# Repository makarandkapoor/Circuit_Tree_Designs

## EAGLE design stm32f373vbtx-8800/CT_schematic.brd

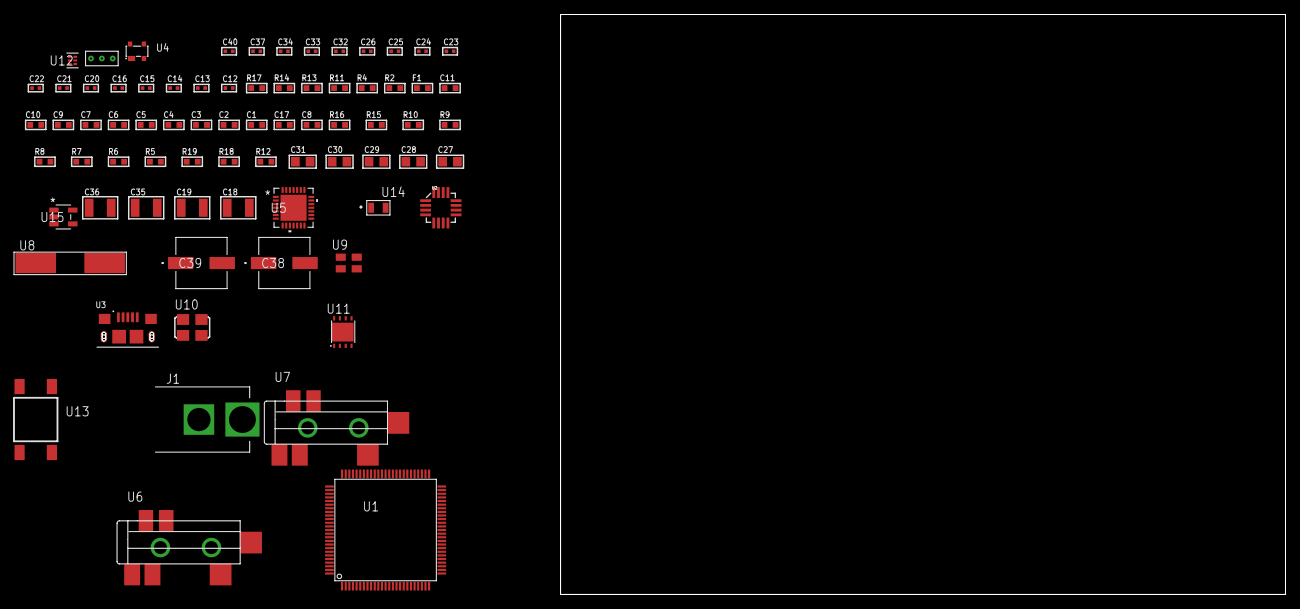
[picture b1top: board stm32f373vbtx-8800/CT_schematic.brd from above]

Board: 2 copper layers, 163.2 x 80.0 mm, 75 parts (0 on the bottom side), 36 nets, no tracks yet.

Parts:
C1, C11: 1e-06; C0603
C2, C3, C4, C5, C6, C7, C9: 1e-07; C0603
C8: 4.7e-06; C0603
C10: 1e-08; C0603
C12, C13: 1e-11; C0402
C14, C15, C16, C32, C33, C34, C40: 1e-08; C0402
C17: 4.7e-07; C0603
C18, C19: 2.2e-05; C1210
C20, C21: 1e-09; C0402
C22, C23, C24, C25, C26, C37: 1e-07; C0402
C27, C28, C29, C30, C31: 1e-05; C0805
C35, C36: 1e-05; C1210
C38, C39: 0.0001; EXV-9H
F1: 240.0; L0603
J1: PJ-037B; PJ-037B_PACKAGE
R2, R14: 1000.0; R0603
R4: 4700.0; R0603
R5, R6, R7, R15, R16: 10000.0; R0603
R8, R9, R10: 47000.0; R0603
R11: 680.0; R0603
R12: 100000.0; R0603
R13: 2231.0; R0603
R17: 9100.0; R0603
R18: 680000.0; R0603
R19: 120000.0; R0603
U1: STM32F373VBT7; LQFP100
U2: l3g4200d; LGA-16
U3: 10118193-0001LF; FCI_10118193-0001LF
U4: prtr5v0u2ax; SOT143B
U5: WM8731CLSEFL; QFN-28
U6, U7: SJ-43515TS-SMT-TR
U8: ABLS-25.000MHZ-B2F-T
U9: ASEK-32.768KHz-ECST; ASEK
U10: ASFL1-12.288MHZ-EC-T; ASFL1
U11: LP3878SDX-ADJ/NOPB; WSON-8
U12: TPS3895ADRYR; SON-6
U13: 4-1437565-2; SW_4-1437565-2
U14: Q65110A2395; LGM67K-G1J2-24-Z
U15: nc7sz125m5x; NC7SZ125M5X
U16: Dummy; DUMMY_PACKAGE_163

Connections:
CLK_CRYSTAL_U1_12: C12.1, U1.12, U8.1
CLK_CRYSTAL_U1_13: C13.1, U1.13, U8.2
CLK_U1_8: U1.8, U9.3
CLK_U5_1: U5.1, U10.3
GND: C1.2, C2.2, C3.2, C4.2, C5.2, C6.2, C7.2, C8.2, C9.2, C10.2, C11.2, C12.2, C13.2, C14.2, C15.2, C16.2, C21.2, C22.2, C23.2, C24.2, C25.2, C26.2, C27.2, C28.2, C29.2, C30.2, C31.2, C32.2, C33.2, C34.2, C35.2, C36.2, C37.2, C38.2, C39.2, C40.2, J1.2, R2.2, R5.2, R6.1, R6.2, R8.2, R9.2, R10.2, R14.2, R17.2, R19.2, U1.20, U1.74, U1.99, U2.8, U2.9, U2.10, U2.11, U2.12, U2.13, U3.5, U3.6, U3.7, U3.8, U3.9, U4.1, U5.4, U5.15, U5.19, U5.25, U5.26, U5.29, U6.1, U7.1, U9.2, U10.2, U11.3, U11.PAD, U12.2, U14.C, U15.1, U15.3, U16.1
NET_U1_14: R4.1, U1.14, U15.4
NET_U1_21: C10.1, C11.1, F1.1, U1.21, U1.22, U1.50, U1.51
NET_U1_49: C9.1, U1.48, U1.49
NET_U1_94: R5.1, U1.94
NET_U1_98: U13.3, U13.4
NET_U2_14: C16.1, C17.1, U2.14
NET_U4_4: U3.1, U4.4
NET_U5_20: C26.1, C31.1, U5.20
NET_U6_2: C19.1, R9.1, U6.2
NET_U6_5: C18.1, R8.1, U6.5
NET_U7_5: C20.1, C21.1, R10.1, R11.1, U7.5
NET_U11_1: C34.1, U11.1
NET_U11_6: R13.2, R14.1, U11.6
NET_U11_8: R12.1, U11.8
NET_U12_1: R16.1, R17.1, U12.1
NET_U12_3: R18.2, R19.1, U12.3
NET_U12_4: R15.1, U12.4, U15.2
NET_U13_1: R2.1, U13.1, U13.2
PROC_I2S1_CK: U1.64, U5.7
PROC_I2S1_SD: U1.35, U5.8
PROC_I2S1_WS: U1.63, U5.9, U5.11
PROC_PE2: U1.1, U16.2
PROC_PE3: U1.2, U16.3
PROC_SPI1_MISO: U1.31, U2.4
PROC_SPI1_MOSI: U1.32, U2.3
PROC_SPI1_NSS: R7.1, U1.29, U2.5
PROC_SPI1_SCK: U1.30, U2.2
PROC_USB_DM: U1.70, U3.2, U4.3
PROC_USB_DP: U1.71, U3.3, U4.2
VCC_S1_14V9: C35.1, C38.1, C39.1, J1.1, R12.2, U11.4
VCC_TIER1_3V3: C1.1, C2.1, C3.1, C4.1, C5.1, C6.1, C7.1, C8.1, C14.1, C15.1, C22.1, C23.1, C24.1, C25.1, C27.1, C28.1, C29.1, C30.1, C32.1, C33.1, C36.1, C37.1, C40.1, F1.2, R4.2, R7.2, R13.1, R15.2, R16.2, R18.1, U1.6, U1.28, U1.75, U1.100, U2.1, U2.15, U2.16, U5.3, U5.5, U5.12, U5.18, U9.4, U10.4, U11.5, U12.6, U15.5

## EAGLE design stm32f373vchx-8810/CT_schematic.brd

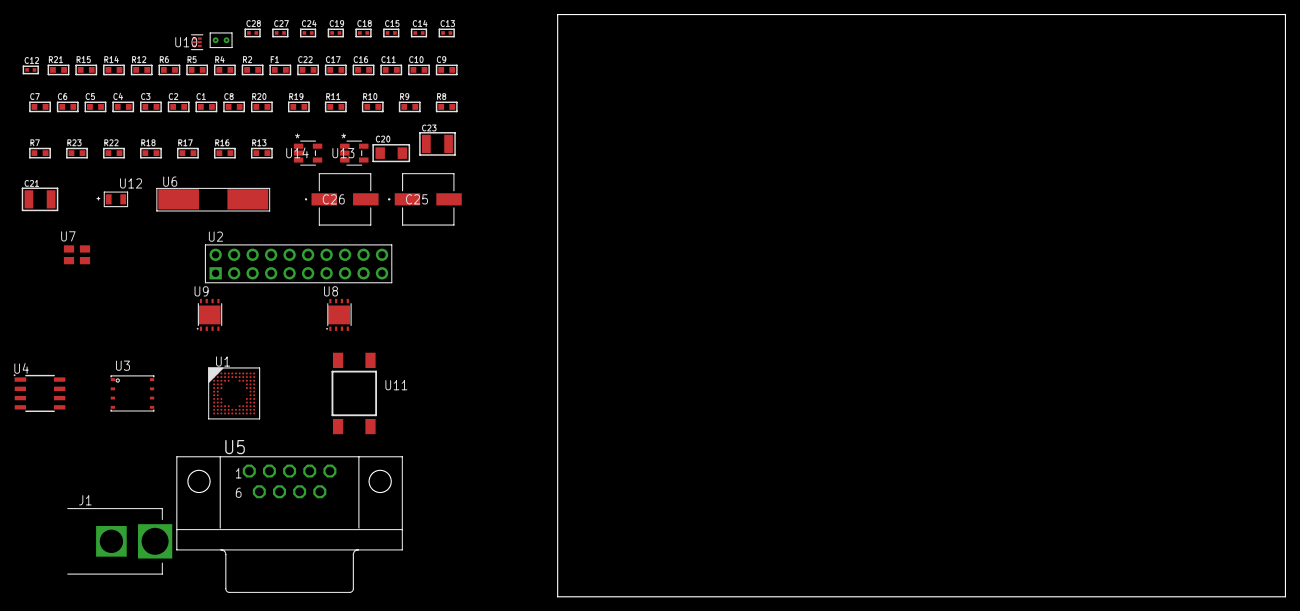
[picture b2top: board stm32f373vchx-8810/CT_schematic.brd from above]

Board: 2 copper layers, 100.0 x 80.0 mm, 66 parts (0 on the bottom side), 36 nets, no tracks yet.

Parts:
C1, C11, C16, C17, C22: 1e-06; C0603
C2, C3, C4, C5, C6, C7, C9: 1e-07; C0603
C8: 4.7e-06; C0603
C10: 1e-08; C0603
C12, C13: 1e-11; C0402
C14, C24: 1e-07; C0402
C15, C18, C19, C27, C28: 1e-08; C0402
C20: 1e-05; C1206
C21, C23: 1e-05; C1210
C25, C26: 0.0001; EXV-9H
F1: 240.0; L0603
J1: PJ-037B; PJ-037B_PACKAGE
R2, R15: 1000.0; R0603
R4: 4700.0; R0603
R5, R6: 2200.0; R0603
R7, R8, R9, R10, R11, R19, R20: 10000.0; R0603
R12: 120.0; R0603
R13, R16, R18: 100000.0; R0603
R14: 2231.0; R0603
R17: 300000.0; R0603
R21: 9100.0; R0603
R22: 680000.0; R0603
R23: 120000.0; R0603
U1: STM32F373VCH7; UFBGA100
U2: TST-110-05-T-D-RA
U3: 24AA512-I/MF; DFN8-S
U4: MCP2562-E/SN; SOIC-8
U5: 182-009-113R531; 182-009-MALE
U6: ABLS-25.000MHZ-B2F-T
U7: ASEK-32.768KHz-ECST; ASEK
U8: LP3878SDX-ADJ/NOPB; WSON-8
U9: LP2951ACSDX/NOPB; WSON-8
U10: TPS3895ADRYR; SON-6
U11: 4-1437565-2; SW_4-1437565-2
U12: Q65110A2395; LGM67K-G1J2-24-Z
U13, U14: nc7sz125m5x; NC7SZ125M5X
U15: Dummy; DUMMY_PACKAGE_149

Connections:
CLK_CRYSTAL_U1_F1: C12.1, U1.F1, U6.1
CLK_CRYSTAL_U1_G1: C13.1, U1.G1, U6.2
CLK_U1_D1: U1.D1, U7.3
GND: C1.2, C2.2, C3.2, C4.2, C5.2, C6.2, C7.2, C8.2, C9.2, C10.2, C11.2, C12.2, C13.2, C14.2, C15.2, C16.2, C17.2, C18.2, C19.2, C20.2, C21.2, C22.2, C23.2, C24.2, C25.2, C26.2, C27.2, C28.2, J1.2, R2.2, R7.2, R9.2, R10.2, R15.2, R18.2, R21.2, R23.2, U1.D3, U1.F11, U1.K1, U2.4, U2.6, U2.8, U2.10, U2.12, U2.14, U2.16, U2.18, U2.20, U3.4, U3.7, U4.2, U4.8, U5.5, U7.2, U8.3, U8.PAD, U9.3, U9.4, U9.PAD, U10.2, U12.C, U13.2, U13.3, U14.1, U14.3, U15.1
NET_U1_A3: R5.1, U1.A3, U3.6
NET_U1_A4: R7.1, U1.A4
NET_U1_B3: R6.1, U1.B3, U3.5
NET_U1_F12: C9.1, U1.F12, U1.L11
NET_U1_H2: R4.1, U1.H2, U14.4
NET_U1_M1: C10.1, C11.1, F1.1, U1.G12, U1.L1, U1.L12, U1.M1
NET_U1_M12: U11.3, U11.4
NET_U3_1: R9.1, U3.1
NET_U3_2: R10.1, U3.2
NET_U3_3: R11.1, U3.3
NET_U4_6: R12.2, U4.6
NET_U5_2: R12.2, U4.6, U5.2
NET_U5_3: R12.1, U4.7, U5.3
NET_U8_1: C19.1, U8.1
NET_U8_6: R14.2, R15.1, U8.6
NET_U8_8: R13.1, U8.8
NET_U9_5: R16.1, U9.5
NET_U9_7: R17.2, R18.1, U9.7
NET_U10_1: R20.1, R21.1, U10.1
NET_U10_3: R22.2, R23.1, U10.3
NET_U10_4: R19.1, U10.4, U13.4, U14.2
NET_U11_1: R2.1, U11.1, U11.2
PROC_CAN_RX: U1.B12, U4.4
PROC_CAN_TX: U1.A12, U4.1
PROC_DAC1_OUT2: U1.K4, U15.2
PROC_SYS_JTCK_SWCLK: U1.A10, U2.9
PROC_SYS_JTDO_TRACESWO: U1.A8, U2.13
PROC_SYS_JTMS_SWDIO: U1.A11, U2.7
RST_OUT_U2_SRESET_B: R8.1, U2.15, U13.1
VCC_S1_10V6: C20.1, C22.1, C25.1, C26.1, J1.1, R13.2, U8.4, U9.8
VCC_TIER1_3V3: C1.1, C2.1, C3.1, C4.1, C5.1, C6.1, C7.1, C8.1, C14.1, C15.1, C17.1, C18.1, C21.1, C24.1, C27.1, C28.1, F1.2, R4.2, R5.2, R6.2, R8.2, R11.2, R14.1, R19.2, R20.2, R22.1, U1.C4, U1.E2, U1.G11, U1.H3, U2.1, U3.8, U4.5, U7.4, U8.5, U10.6, U13.5, U14.5
VCC_TIER1_5V0: C16.1, C23.1, R16.2, R17.1, U4.3, U9.1

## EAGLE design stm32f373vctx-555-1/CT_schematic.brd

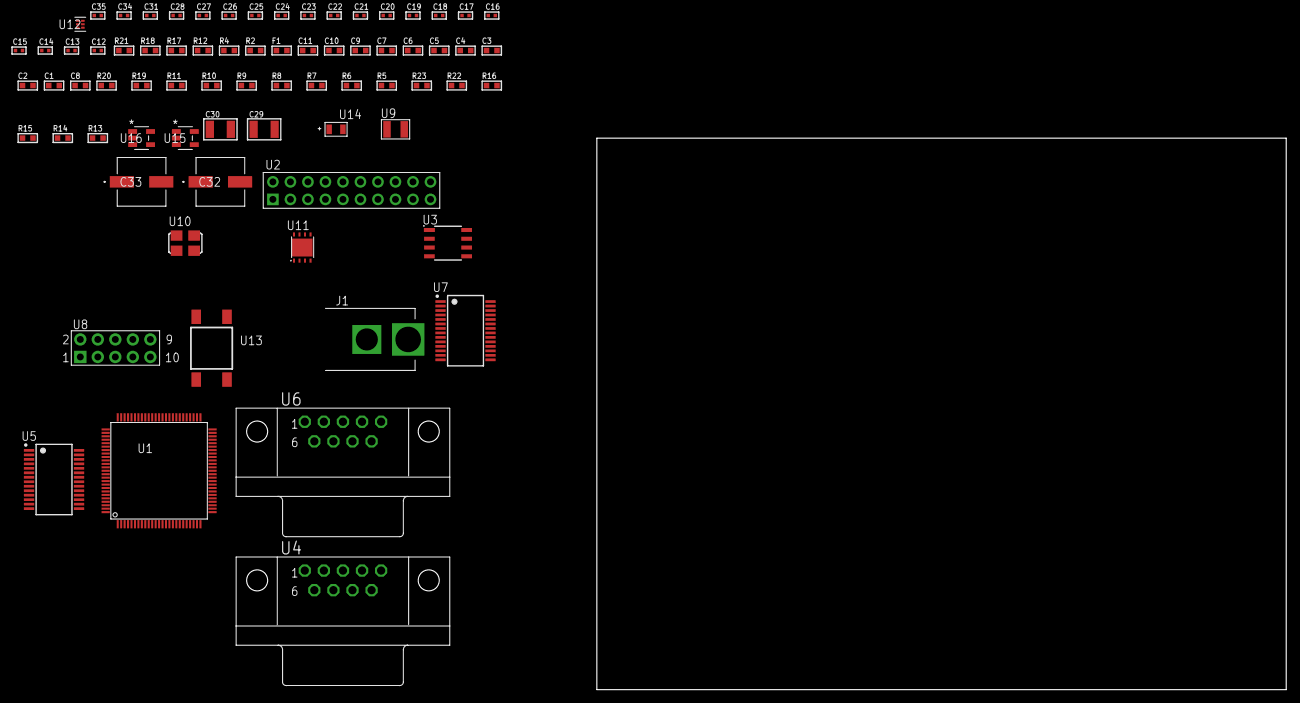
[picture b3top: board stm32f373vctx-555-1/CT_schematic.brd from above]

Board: 2 copper layers, 100.0 x 80.0 mm, 74 parts (0 on the bottom side), 61 nets, no tracks yet.

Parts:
C1, C11: 1e-06; C0603
C2, C3, C4, C5, C6, C7, C9: 1e-07; C0603
C8: 4.7e-06; C0603
C10: 1e-08; C0603
C12, C13: 1e-11; C0402
C14, C15, C16, C17, C18, C19, C20, C21, C22, C23, C24, C25, C26, C31: 1e-07; C0402
C27, C28, C34, C35: 1e-08; C0402
C29, C30: 1e-05; C1210
C32, C33: 0.0001; EXV-9H
F1: 240.0; L0603
J1: PJ-037B; PJ-037B_PACKAGE
R2, R18: 1000.0; R0603
R4: 4700.0; R0603
R5, R6, R7, R8, R9, R10, R11, R19, R20: 10000.0; R0603
R12: 120.0; R0603
R13: 470000.0; R0603
R14, R15, R16: 100000.0; R0603
R17: 2231.0; R0603
R21: 9100.0; R0603
R22: 680000.0; R0603
R23: 120000.0; R0603
U1: STM32F373VCT6; LQFP100
U2: TST-110-05-T-D-RA
U3: SN65HVD230D; SOIC-8
U4, U6: 182-009-113R531; 182-009-MALE
U5, U7: ST3241EBPR; SSOP-28
U8: HTSS-105-01-G-D
U9: ABS07-32.768KHZ-7-T
U10: ASFL1-25MHZ-NCS; ASFL1
U11: LP3878SDX-ADJ/NOPB; WSON-8
U12: TPS3895ADRYR; SON-6
U13: 4-1437565-2; SW_4-1437565-2
U14: Q65110A2395; LGM67K-G1J2-24-Z
U15, U16: nc7sz125m5x; NC7SZ125M5X

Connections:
CLK_CRYSTAL_U1_8: C12.1, U1.8, U9.1
CLK_CRYSTAL_U1_9: C13.1, U1.9, U9.2
CLK_U1_12: U1.12, U10.3
GND: C1.2, C2.2, C3.2, C4.2, C5.2, C6.2, C7.2, C8.2, C9.2, C10.2, C11.2, C12.2, C13.2, C14.2, C15.2, C16.2, C17.2, C20.2, C21.2, C22.2, C25.2, C26.2, C27.2, C28.2, C29.2, C30.2, C31.2, C32.2, C33.2, C34.2, C35.2, J1.2, R2.2, R5.2, R11.2, R13.2, R18.2, R21.2, R23.2, U1.20, U1.74, U1.99, U2.4, U2.6, U2.8, U2.10, U2.12, U2.14, U2.16, U2.18, U2.20, U3.2, U4.5, U5.23, U5.25, U6.5, U7.23, U7.25, U8.9, U10.2, U11.3, U11.PAD, U12.2, U14.C, U15.2, U15.3, U16.1, U16.3
NET_U1_14: R4.1, U1.14, U16.4
NET_U1_21: C10.1, C11.1, F1.1, U1.21, U1.22, U1.50, U1.51
NET_U1_49: C9.1, U1.48, U1.49
NET_U1_94: R5.1, U1.94
NET_U1_98: U13.3, U13.4
NET_U2_19: R11.1, U2.19
NET_U3_6: R12.2, U3.6
NET_U3_8: R13.1, U3.8
NET_U4_2: R12.2, U3.6, U4.2
NET_U4_3: R12.1, U3.7, U4.3
NET_U5_1: C19.1, U5.1
NET_U5_2: C19.2, U5.2
NET_U5_3: C21.1, U5.3
NET_U5_22: R14.1, U5.22
NET_U5_24: C18.2, U5.24
NET_U5_27: C20.1, U5.27
NET_U5_28: C18.1, U5.28
NET_U6_2: U5.4, U6.2
NET_U6_3: U5.9, U6.3
NET_U6_7: U5.5, U6.7
NET_U6_8: U5.10, U6.8
NET_U7_1: C24.1, U7.1
NET_U7_2: C24.2, U7.2
NET_U7_3: C26.1, U7.3
NET_U7_22: R15.1, U7.22
NET_U7_24: C23.2, U7.24
NET_U7_27: C25.1, U7.27
NET_U7_28: C23.1, U7.28
NET_U8_3: U7.4, U8.3
NET_U8_4: U7.5, U8.4
NET_U8_5: U7.9, U8.5
NET_U8_6: U7.10, U8.6
NET_U11_1: C28.1, U11.1
NET_U11_6: R17.2, R18.1, U11.6
NET_U11_8: R16.1, U11.8
NET_U12_1: R20.1, R21.1, U12.1
NET_U12_3: R22.2, R23.1, U12.3
NET_U12_4: R19.1, U12.4, U15.4, U16.2
NET_U13_1: R2.1, U13.1, U13.2
PROC_CAN_RX: U1.81, U3.4
PROC_CAN_TX: U1.82, U3.1
PROC_SYS_JTCK_SWCLK: R9.1, U1.76, U2.9
PROC_SYS_JTDI: R7.1, U1.77, U2.5
PROC_SYS_JTDO_TRACESWO: U1.89, U2.13
PROC_SYS_JTMS_SWDIO: R8.1, U1.72, U2.7
PROC_SYS_NJTRST: R6.1, U1.90, U2.3
PROC_USART1_CTS: U1.70, U5.13
PROC_USART1_RTS: U1.71, U5.18
PROC_USART1_RX: U1.34, U5.19
PROC_USART1_TX: U1.33, U5.14
PROC_USART2_CTS: U1.23, U7.13
PROC_USART2_RTS: U1.24, U7.18
PROC_USART2_RX: U1.26, U7.19
PROC_USART2_TX: U1.25, U7.14
RST_OUT_U2_SRESET_B: R10.1, U2.15, U15.1
VCC_S1_14V5: C29.1, C32.1, C33.1, J1.1, R16.2, U11.4
VCC_TIER1_3V3: C1.1, C2.1, C3.1, C4.1, C5.1, C6.1, C7.1, C8.1, C14.1, C15.1, C16.1, C17.1, C22.1, C27.1, C30.1, C31.1, C34.1, C35.1, F1.2, R4.2, R6.2, R7.2, R8.2, R9.2, R10.2, R14.2, R15.2, R17.1, R19.2, R20.2, R22.1, U1.6, U1.28, U1.75, U1.100, U2.1, U2.2, U3.3, U5.26, U7.26, U10.4, U11.5, U12.6, U15.5, U16.5

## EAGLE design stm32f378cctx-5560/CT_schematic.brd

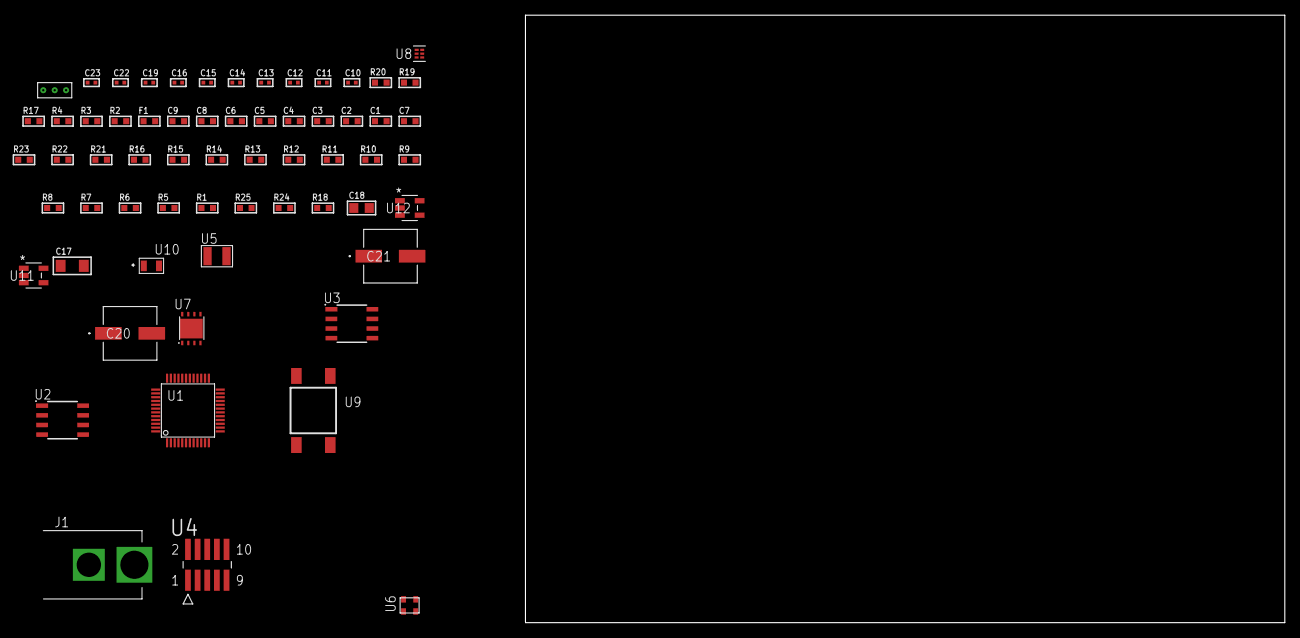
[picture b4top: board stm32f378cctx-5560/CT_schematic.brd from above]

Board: 2 copper layers, 100.0 x 80.0 mm, 63 parts (0 on the bottom side), 39 nets, no tracks yet.

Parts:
C1, C9: 1e-06; C0603
C2, C3, C4, C5, C6: 1e-07; C0603
C7: 4.7e-06; C0603
C8: 1e-08; C0603
C10, C11: 1e-11; C0402
C12, C13, C15, C16, C22, C23: 1e-08; C0402
C14, C19: 1e-07; C0402
C17: 1e-05; C1206
C18: 1e-05; C0805
C20, C21: 0.0001; EXV-9H
F1: 240.0; L0603
J1: PJ-037B; PJ-037B_PACKAGE
R1, R5, R6, R7, R8, R9, R10, R11, R12, R13, R14, R15, R16, R21, R22: 10000.0; R0603
R2, R20: 1000.0; R0603
R3: 910.0; R0603
R4: 4700.0; R0603
R17: 5.0; R0603
R18: 100000.0; R0603
R19: 806.0; R0603
R23: 82000.0; R0603
R24: 300000.0; R0603
R25: 120000.0; R0603
U1: STM32F378CCT6; LQFP48
U2: AT25160B-SSHL-T; SOIC-8
U3: AT25512N-SH-T; SOIC-8
U4: FTSH-105-01-L-DV-K; SAMTEC_FTSH-105-01-L-DV-K
U5: ABS07-32.768KHZ-7-T
U6: ASDMB-25.000MHZ-EC-T; ASDMB-XX.XXXXMHZ-XX-XX-XXX
U7: LP3878SDX-ADJ/NOPB; WSON-8
U8: TPS3895ADRYR; SON-6
U9: 4-1437565-2; SW_4-1437565-2
U10: Q65110A2395; LGM67K-G1J2-24-Z
U11, U12: nc7sz125m5x; NC7SZ125M5X
U13: Dummy; DUMMY_PACKAGE_132

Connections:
CLK_CRYSTAL_U1_3: C10.1, U1.3, U5.1
CLK_CRYSTAL_U1_4: C11.1, U1.4, U5.2
CLK_U1_5: U1.5, U6.3
GND: C1.2, C2.2, C3.2, C4.2, C5.2, C6.2, C7.2, C8.2, C9.2, C10.2, C11.2, C12.2, C13.2, C14.2, C15.2, C16.2, C17.2, C18.2, C19.2, C20.2, C21.2, C22.2, C23.2, J1.2, R2.2, R5.2, R6.2, R16.2, R17.2, R20.2, R23.2, R25.2, U1.8, U1.23, U1.47, U2.4, U3.4, U4.3, U4.5, U6.2, U7.3, U7.PAD, U8.2, U10.C, U11.2, U11.3, U12.1, U12.3, U13.1
NET_U1_7: R4.1, U1.7, U12.4
NET_U1_9: C8.1, C9.1, F1.1, U1.9, U1.24
NET_U1_20: R6.1, U1.20
NET_U1_44: R5.1, U1.44
NET_U1_45: R3.1, U1.45, U10.A
NET_U1_46: R1.1, U1.46, U9.3, U9.4
NET_U2_3: R7.1, U2.3
NET_U2_7: R9.1, U2.7
NET_U3_3: R10.1, U3.3
NET_U3_7: R12.1, U3.7
NET_U4_9: R17.1, U4.9
NET_U7_1: C16.1, U7.1
NET_U7_6: R19.2, R20.1, U7.6
NET_U7_8: R18.1, U7.8
NET_U8_1: R22.1, R23.1, U8.1
NET_U8_3: R24.2, R25.1, U8.3
NET_U8_4: R21.1, U8.4, U11.4, U12.2
NET_U9_1: R2.1, U9.1, U9.2
PROC_ADC1_IN1: U1.11, U13.3
PROC_ADC1_IN2: U1.12, U13.2
PROC_SPI1_MISO: U1.16, U3.2
PROC_SPI1_MOSI: U1.18, U3.5
PROC_SPI1_NSS: R11.1, U1.14, U3.1
PROC_SPI1_SCK: U1.15, U3.6
PROC_SPI2_MISO: U1.26, U2.2
PROC_SPI2_MOSI: U1.27, U2.5
PROC_SPI2_NSS: R8.1, U1.32, U2.1
PROC_SPI2_SCK: U1.28, U2.6
PROC_SYS_JTCK_SWCLK: R16.1, U1.37, U4.4
PROC_SYS_JTDI: R14.1, U1.38, U4.8
PROC_SYS_JTDO_TRACESWO: U1.39, U4.6
PROC_SYS_JTMS_SWDIO: R15.1, U1.34, U4.2
RST_OUT_U4_JTAG_RST_B: R13.1, U4.10, U11.1
VCC_S1_9V8: C17.1, C20.1, C21.1, J1.1, R18.2, U7.4
VCC_TIER1_1V8: C1.1, C2.1, C3.1, C4.1, C5.1, C6.1, C7.1, C12.1, C13.1, C14.1, C15.1, C18.1, C19.1, C22.1, C23.1, F1.2, R1.2, R3.2, R4.2, R7.2, R8.2, R9.2, R10.2, R11.2, R12.2, R13.2, R14.2, R15.2, R19.1, R21.2, R22.2, R24.1, U1.1, U1.17, U1.48, U2.8, U3.8, U4.1, U6.4, U7.5, U8.6, U11.5, U12.5

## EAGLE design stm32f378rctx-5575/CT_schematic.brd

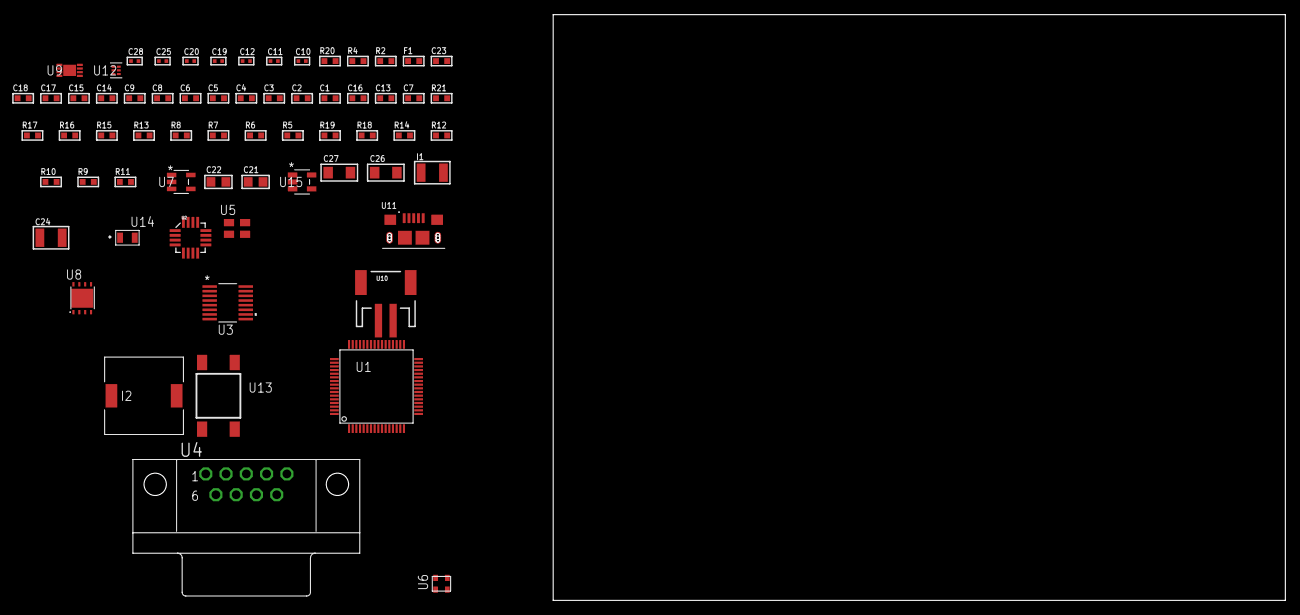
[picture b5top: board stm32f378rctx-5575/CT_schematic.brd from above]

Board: 2 copper layers, 122.6 x 80.0 mm, 65 parts (0 on the bottom side), 41 nets, no tracks yet.

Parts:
C1, C9, C14, C15, C17, C18, C23: 1e-06; C0603
C2, C3, C4, C5, C6: 1e-07; C0603
C7: 4.7e-06; C0603
C8: 1e-08; C0603
C10, C11, C12, C19, C20, C28: 1e-08; C0402
C13: 4.7e-07; C0603
C16: 2.2e-07; C0603
C21, C22: 1e-05; C0805
C24: 1e-05; C1210
C25: 1e-07; C0402
C26, C27: 1e-05; C1206
F1: 240.0; L0603
I1: 1e-05; L1210
I2: 5.2e-06; DR1040
R2: 1000.0; R0603
R4: 4700.0; R0603
R5, R6, R7, R8, R15, R16, R21: 10000.0; R0603
R9, R12, R14: 100000.0; R0603
R10: 490000.0; R0603
R11: 1000000.0; R0603
R13: 91000.0; R0603
R17: 82000.0; R0603
R18: 300000.0; R0603
R19: 120000.0; R0603
R20: 2000.0; R0603
U1: STM32F378RCT6; LQFP64
U2: l3g4200d; LGA-16
U3: LTC2804CGN-1#PBF; SSOP-16
U4: 182-009-113R531; 182-009-MALE
U5: ASEK-2-32.768KHz-ECST; ASEK
U6: ASDMB-25.000MHZ-EC-T; ASDMB-XX.XXXXMHZ-XX-XX-XXX
U7: ltc3406es5; TSOT-23-5
U8: LP2951ACSDX/NOPB; WSON-8
U9: MCP73831T-2ACI/MC; DFN8_2X3MC
U10: S2B-PH-SM4-TB(LF)(SN); JST-2-SMD
U11: 10118193-0001LF; FCI_10118193-0001LF
U12: TPS3895ADRYR; SON-6
U13: 4-1437565-2; SW_4-1437565-2
U14: Q65110A2395; LGM67K-G1J2-24-Z
U15: nc7sz125m5x; NC7SZ125M5X

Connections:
CLK_U1_3: U1.3, U5.3
CLK_U1_5: U1.5, U6.3
GND: C1.2, C2.2, C3.2, C4.2, C5.2, C6.2, C7.2, C8.2, C9.2, C10.2, C11.2, C12.2, C14.2, C15.2, C17.2, C18.2, C19.2, C20.2, C21.2, C22.1, C22.2, C23.2, C24.2, C25.2, C26.2, C27.2, C28.2, R2.2, R5.2, R6.2, R7.1, R7.2, R10.2, R14.2, R17.2, R19.2, R20.2, U1.12, U1.31, U1.63, U2.8, U2.9, U2.10, U2.11, U2.12, U2.13, U3.8, U4.5, U5.2, U6.2, U7.2, U8.3, U8.4, U8.PAD, U9.6, U9.9, U10.2, U11.5, U11.6, U11.7, U11.8, U11.9, U12.2, U14.C, U15.1, U15.3
INPUT_USBPOWER_5V: C26.1, R21.2, U9.1, U9.2, U11.1
NET_U1_7: R4.1, U1.7, U15.4
NET_U1_13: C8.1, C9.1, F1.1, U1.13, U1.17, U1.32
NET_U1_28: R6.1, U1.28
NET_U1_60: R5.1, U1.60
NET_U1_62: U13.3, U13.4
NET_U2_14: C12.1, C13.1, U2.14
NET_U3_6: C14.1, U3.6
NET_U3_7: C16.1, I1.2, U3.7
NET_U3_9: C15.1, U3.9
NET_U3_10: C16.2, U3.10
NET_U3_11: R9.1, U3.11
NET_U4_2: U3.1, U4.2
NET_U4_3: U3.3, U4.3
NET_U4_7: U3.2, U4.7
NET_U4_8: U3.4, U4.8
NET_U7_3: I2.1, U7.3
NET_U7_5: R10.1, R11.1, U7.5
NET_U7_ATNET_3: I2.2, R11.2
NET_U8_5: R12.1, U8.5
NET_U8_7: R13.2, R14.1, U8.7
NET_U9_5: R21.1, U9.5
NET_U9_8: R20.1, U9.8
NET_U12_1: R16.1, R17.1, U12.1
NET_U12_3: R18.2, R19.1, U12.3
NET_U12_4: R15.1, U12.4, U15.2
NET_U13_1: R2.1, U13.1, U13.2
PROC_SPI1_MISO: U1.22, U2.4
PROC_SPI1_MOSI: U1.23, U2.3
PROC_SPI1_NSS: R8.1, U1.20, U2.5
PROC_SPI1_SCK: U1.21, U2.2
PROC_USART1_CTS: U1.44, U3.13
PROC_USART1_RTS: U1.45, U3.15
PROC_USART1_RX: U1.25, U3.16
PROC_USART1_TX: U1.24, U3.14
VCC_S1_3V7: C21.1, C23.1, C27.1, U7.4, U8.8, U9.3, U9.4, U10.1
VCC_TIER1_1V8: C1.1, C2.1, C3.1, C4.1, C5.1, C6.1, C7.1, C11.1, C17.1, C18.1, C19.1, C20.1, C22.2, C25.1, C28.1, F1.2, I1.1, I2.2, R4.2, R8.2, R9.2, R11.2, R15.2, R16.2, R18.1, U1.1, U1.19, U1.64, U2.1, U3.5, U3.12, U5.4, U6.4, U12.6, U15.5
VCC_TIER1_2V5: C10.1, C24.1, R12.2, R13.1, U2.15, U2.16, U8.1

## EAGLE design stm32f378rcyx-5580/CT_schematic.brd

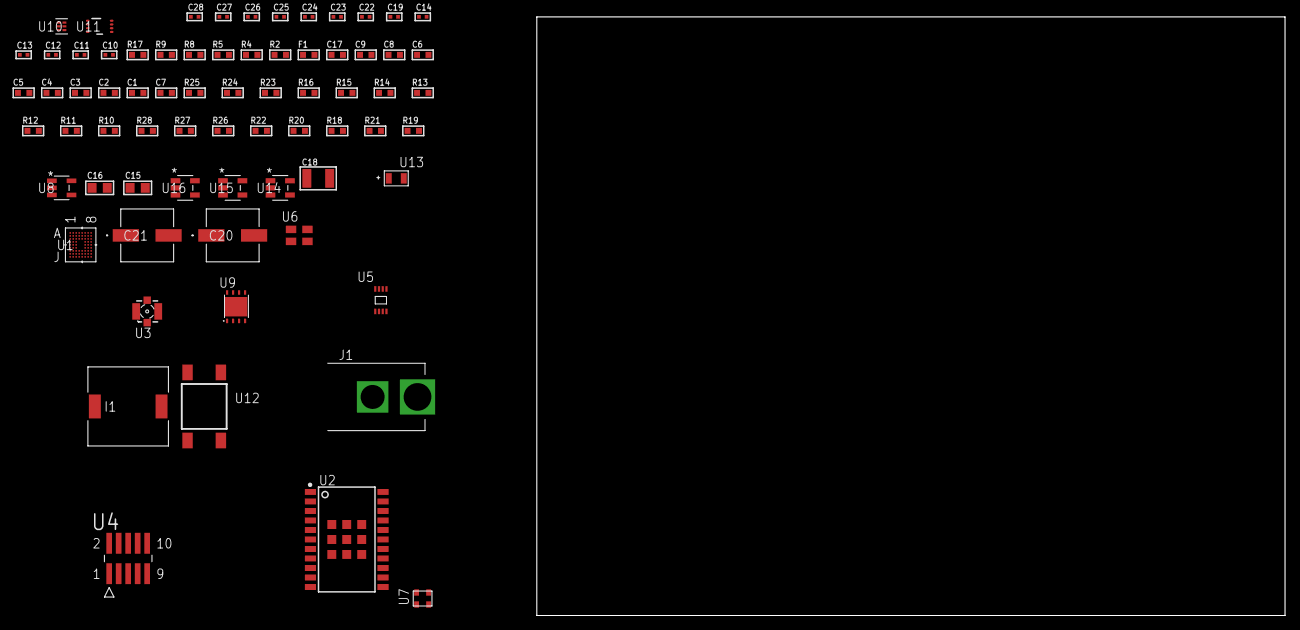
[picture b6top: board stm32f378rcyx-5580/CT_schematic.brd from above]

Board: 2 copper layers, 100.0 x 80.0 mm, 71 parts (0 on the bottom side), 36 nets, no tracks yet.

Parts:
C1, C9, C17: 1e-06; C0603
C2, C3, C4, C5, C6: 1e-07; C0603
C7: 4.7e-06; C0603
C8: 1e-08; C0603
C10, C11, C19, C23, C25: 1e-07; C0402
C12, C13, C14, C22, C24, C26, C27, C28: 1e-08; C0402
C15, C16: 1e-05; C0805
C18: 1e-05; C1210
C20, C21: 0.0001; EXV-9H
F1: 240.0; L0603
I1: 7e-06; DR1040
J1: PJ-037B; PJ-037B_PACKAGE
R2: 1000.0; R0603
R4, R5: 4700.0; R0603
R8, R9: 2200.0; R0603
R10, R11, R12, R13, R14, R15, R16, R23, R24: 10000.0; R0603
R17: 5.0; R0603
R18: 490000.0; R0603
R19: 1000000.0; R0603
R20, R22: 100000.0; R0603
R21: 153694.38; R0603
R25: 82000.0; R0603
R26: 300000.0; R0603
R27: 120000.0; R0603
R28: 200000.0; R0603
U1: STM32F378RCY6; WLCSP66_8X8
U2: A2200-A
U3: 73412-0114; COAXIAL_C
U4: FTSH-105-01-L-DV-K; SAMTEC_FTSH-105-01-L-DV-K
U5: 24AA04-I/MC; TDFN-8/6MM
U6: ASEK-2-32.768KHz-ECST; ASEK
U7: ASDMB-25.000MHZ-EC-T; ASDMB-XX.XXXXMHZ-XX-XX-XXX
U8: ltc3406es5; TSOT-23-5
U9: LP2951ACSDX/NOPB; WSON-8
U10: TPS3895ADRYR; SON-6
U11: LSF0102DCTR; DCU0008A_N
U12: 4-1437565-2; SW_4-1437565-2
U13: Q65110A2395; LGM67K-G1J2-24-Z
U14, U15, U16: nc7sz125m5x; NC7SZ125M5X

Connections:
CLK_U1_C8: U1.C8, U6.3
CLK_U1_D7: U1.D7, U7.3
GND: C1.2, C2.2, C3.2, C4.2, C5.2, C6.2, C7.2, C8.2, C9.2, C10.2, C11.2, C12.2, C13.2, C14.2, C15.2, C16.1, C16.2, C17.2, C18.2, C19.2, C20.2, C21.2, C22.2, C23.2, C24.2, C25.2, C26.2, C27.2, C28.2, J1.2, R2.2, R10.2, R11.2, R16.2, R17.2, R18.2, R22.2, R25.2, R27.2, U1.C6, U1.G4, U1.G5, U1.G8, U1.J1, U2.7, U2.8, U2.23, U2.24, U2.25, U2.26, U2.27, U2.28, U2.29, U2.30, U2.31, U4.3, U4.5, U5.4, U6.2, U7.2, U8.2, U9.3, U9.4, U9.PAD, U10.2, U11.1, U13.C, U14.2, U14.3, U15.1, U15.3, U16.1, U16.3
NET_U1_B1: R9.1, U1.B1, U5.5
NET_U1_B2: R8.1, U1.B2, U5.6
NET_U1_C7: R10.1, U1.C7
NET_U1_E7: R5.1, U1.E7, U16.4
NET_U1_G2: R11.1, U1.G2
NET_U1_G7: C8.1, C9.1, F1.1, U1.G6, U1.G7, U1.H1
NET_U1_J8: U12.3, U12.4
NET_U2_2: R12.2, U2.2
NET_U2_17: R12.1, U2.17
NET_U2_22: R4.1, U2.22, U15.4
NET_U3_1: U2.11, U3.1
NET_U3_2: U2.10, U3.2, U3.3, U3.4
NET_U4_9: R17.1, U4.9
NET_U8_3: I1.1, U8.3
NET_U8_5: R18.1, R19.1, U8.5
NET_U8_ATNET_3: I1.2, R19.2
NET_U9_5: R20.1, U9.5
NET_U9_7: R21.2, R22.1, U9.7
NET_U10_1: R24.1, R25.1, U10.1
NET_U10_3: R26.2, R27.1, U10.3
NET_U10_4: R23.1, U10.4, U14.4, U15.2, U16.2
NET_U11_8: R28.1, U11.8
NET_U12_1: R2.1, U12.1, U12.2
PROC_I2C1_SCL_TOXCVR: U2.15, U11.5
PROC_I2C1_SDA_TOXCVR: U2.16, U11.6
PROC_SYS_JTCK_SWCLK: R16.1, U1.A1, U4.4
PROC_SYS_JTDI: R14.1, U1.A2, U4.8
PROC_SYS_JTDO_TRACESWO: U1.C5, U4.6
PROC_SYS_JTMS_SWDIO: R15.1, U1.C4, U4.2
RST_OUT_U4_JTAG_RST_B: R13.1, U4.10, U14.1
VCC_S1_4V8: C15.1, C17.1, C20.1, C21.1, J1.1, U8.4, U9.8
VCC_TIER1_1V8: C1.1, C2.1, C3.1, C4.1, C5.1, C6.1, C7.1, C11.1, C12.1, C13.1, C14.1, C16.2, C19.1, C24.1, C25.1, C26.1, C27.1, C28.1, F1.2, I1.2, R5.2, R8.2, R9.2, R13.2, R14.2, R15.2, R19.2, R23.2, R24.2, R26.1, U1.A8, U1.D6, U1.J7, U4.1, U5.7, U5.8, U6.4, U7.4, U10.6, U11.2, U14.5, U15.5, U16.5
VCC_TIER1_3V3: C10.1, C18.1, C22.1, C23.1, R4.2, R20.2, R21.1, R28.2, U2.20, U9.1, U11.7

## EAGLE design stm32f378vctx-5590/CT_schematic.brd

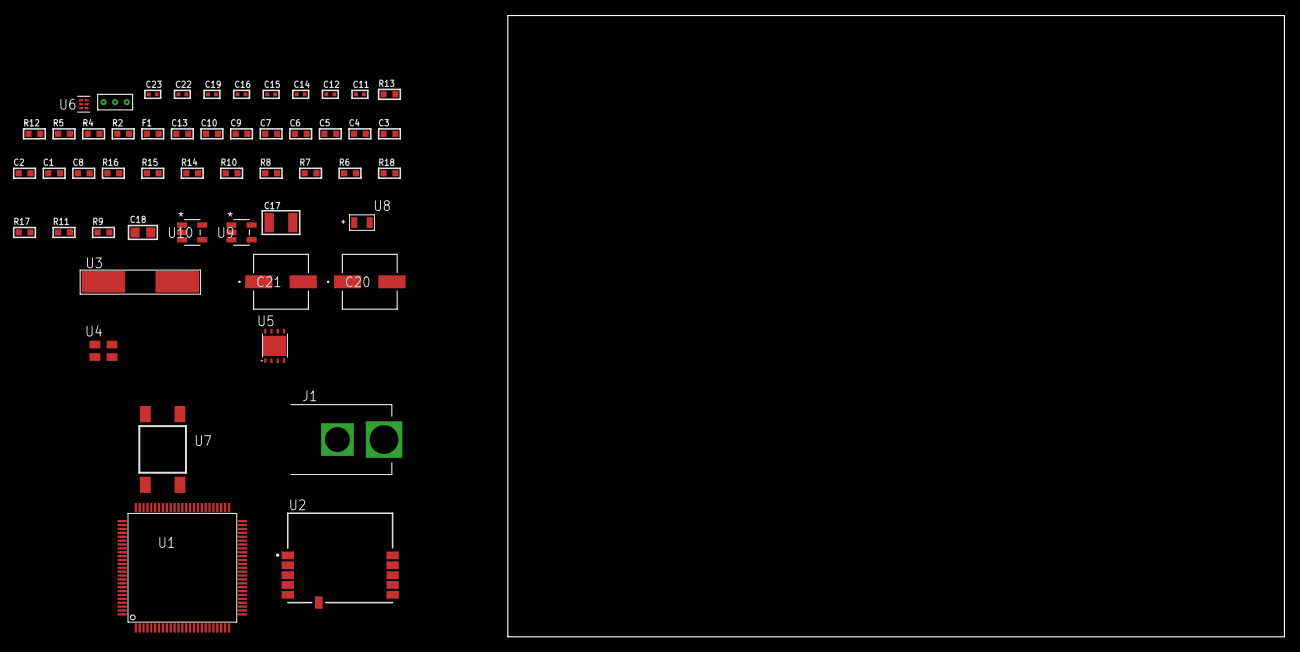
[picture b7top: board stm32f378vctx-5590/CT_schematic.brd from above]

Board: 2 copper layers, 100.0 x 80.0 mm, 52 parts (0 on the bottom side), 26 nets, no tracks yet.

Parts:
C1, C10, C13: 1e-06; C0603
C2, C3, C4, C5, C6, C7: 1e-07; C0603
C8: 4.7e-06; C0603
C9: 1e-08; C0603
C11, C12: 1e-11; C0402
C14, C19: 1e-07; C0402
C15, C16, C22, C23: 1e-08; C0402
C17: 1e-05; C1210
C18: 1e-05; C0805
C20, C21: 0.0001; EXV-9H
F1: 240.0; L0603
J1: PJ-037B; PJ-037B_PACKAGE
R2, R13: 1000.0; R0603
R4, R5: 4700.0; R0603
R6, R7, R8, R14, R15: 10000.0; R0603
R9, R11: 100000.0; R0603
R10: 47000.0; R0603
R12: 806.0; R0603
R16: 82000.0; R0603
R17: 300000.0; R0603
R18: 120000.0; R0603
U1: STM32F378VCT6; LQFP100
U2: SPBTLE-RF; XCVR_SPBTLE-RF
U3: ABLS-25.000MHZ-B2F-T
U4: ASEK-2-32.768KHz-ECST; ASEK
U5: LP3878SDX-ADJ/NOPB; WSON-8
U6: TPS3895ADRYR; SON-6
U7: 4-1437565-2; SW_4-1437565-2
U8: Q65110A2395; LGM67K-G1J2-24-Z
U9, U10: nc7sz125m5x; NC7SZ125M5X
U11: Dummy; DUMMY_PACKAGE_111

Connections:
CLK_CRYSTAL_U1_12: C11.1, U1.12, U3.1
CLK_CRYSTAL_U1_13: C12.1, U1.13, U3.2
CLK_U1_8: U1.8, U4.3
GND: C1.2, C2.2, C3.2, C4.2, C5.2, C6.2, C7.2, C8.2, C9.2, C10.2, C11.2, C12.2, C13.2, C14.2, C15.2, C16.2, C17.2, C18.2, C19.2, C20.2, C21.2, C22.2, C23.2, J1.2, R2.2, R6.2, R7.2, R9.2, R10.2, R13.2, R16.2, R18.2, U1.20, U1.48, U1.49, U1.74, U1.99, U2.6, U4.2, U5.3, U5.PAD, U6.2, U8.C, U9.1, U9.3, U10.1, U10.3, U11.1
NET_U1_14: R5.1, U1.14, U10.4
NET_U1_21: C9.1, C10.1, F1.1, U1.21, U1.22, U1.50, U1.51, U1.52
NET_U1_37: R7.1, U1.37
NET_U1_94: R6.1, U1.94
NET_U1_98: U7.3, U7.4
NET_U2_11: R4.1, U2.11, U9.4
NET_U5_1: C16.1, U5.1
NET_U5_6: R12.2, R13.1, U5.6
NET_U5_8: R11.1, U5.8
NET_U6_1: R15.1, R16.1, U6.1
NET_U6_3: R17.2, R18.1, U6.3
NET_U6_4: R14.1, U6.4, U9.2, U10.2
NET_U7_1: R2.1, U7.1, U7.2
PROC_GPIO_TO_U2_SPI_IRQ: R10.1, U1.1, U2.4
PROC_PE3: U1.2, U11.2
PROC_PE4: U1.3, U11.3
PROC_SPI1_MISO: U1.31, U2.8
PROC_SPI1_MOSI: U1.32, U2.9
PROC_SPI1_NSS: R8.1, U1.29, U2.10
PROC_SPI1_SCK: R9.1, U1.30, U2.7
VCC_S1_14V5: C17.1, C20.1, C21.1, J1.1, R11.2, U5.4
VCC_TIER1_1V8: C1.1, C2.1, C3.1, C4.1, C5.1, C6.1, C7.1, C8.1, C13.1, C14.1, C15.1, C18.1, C19.1, C22.1, C23.1, F1.2, R4.2, R5.2, R8.2, R12.1, R14.2, R15.2, R17.1, U1.6, U1.28, U1.75, U1.100, U2.5, U4.4, U5.5, U6.6, U9.5, U10.5

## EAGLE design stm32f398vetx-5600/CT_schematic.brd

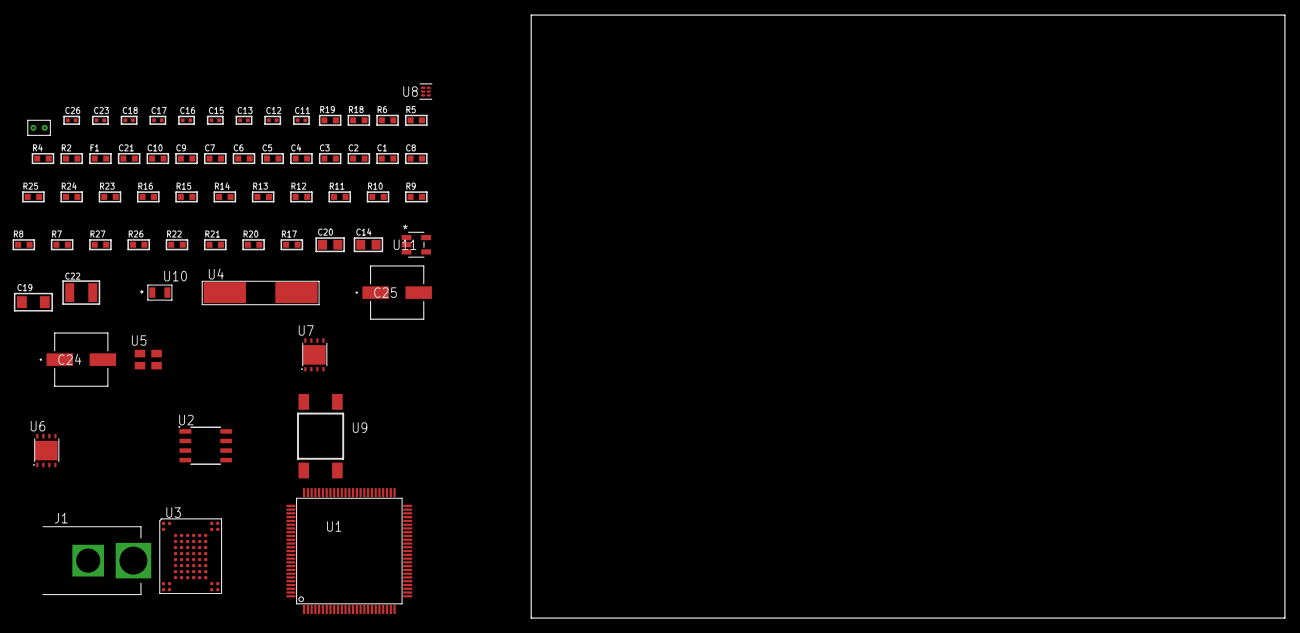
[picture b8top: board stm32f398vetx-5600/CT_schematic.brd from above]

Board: 2 copper layers, 100.0 x 80.0 mm, 65 parts (0 on the bottom side), 32 nets, no tracks yet.

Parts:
C1, C10, C21: 1e-06; C0603
C2, C3, C4, C5, C6, C7: 1e-07; C0603
C8: 4.7e-06; C0603
C9: 1e-08; C0603
C11, C12: 1e-11; C0402
C13, C17, C18, C26: 1e-08; C0402
C14, C20: 1e-05; C0805
C15, C16, C23: 1e-07; C0402
C19: 1e-05; C1206
C22: 1e-05; C1210
C24, C25: 0.0001; EXV-9H
F1: 240.0; L0603
J1: PJ-037B; PJ-037B_PACKAGE
R2, R19: 1000.0; R0603
R4: 4700.0; R0603
R5, R6: 2200.0; R0603
R7, R8, R9, R10, R11, R12, R13, R14, R15, R16, R23, R24: 10000.0; R0603
R17, R20, R22: 100000.0; R0603
R18: 806.0; R0603
R21: 130000.0; R0603
R25: 82000.0; R0603
R26: 300000.0; R0603
R27: 120000.0; R0603
U1: STM32F398VET6; LQFP100
U2: 24AA1025T-I/SN; SOIC-8
U3: TH58NVG3S0HBAI4
U4: ABLS-25.000MHZ-B2F-T
U5: ASEK-2-32.768KHz-ECST; ASEK
U6: LP3878SDX-ADJ/NOPB; WSON-8
U7: LP2951ACSDX/NOPB; WSON-8
U8: TPS3895ADRYR; SON-6
U9: 4-1437565-2; SW_4-1437565-2
U10: Q65110A2395; LGM67K-G1J2-24-Z
U11: nc7sz125m5x; NC7SZ125M5X
U12: Dummy; DUMMY_PACKAGE_144

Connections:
CLK_CRYSTAL_U1_12: C11.1, U1.12, U4.1
CLK_CRYSTAL_U1_13: C12.1, U1.13, U4.2
CLK_U1_8: U1.8, U5.3
GND: C1.2, C2.2, C3.2, C4.2, C5.2, C6.2, C7.2, C8.2, C9.2, C10.2, C11.2, C12.2, C13.2, C14.2, C15.2, C16.2, C17.2, C18.2, C19.2, C20.2, C21.2, C22.2, C23.2, C24.2, C25.2, C26.2, J1.2, R2.2, R7.2, R8.2, R19.2, R22.2, R25.2, R27.2, U1.20, U1.27, U1.49, U1.74, U1.99, U2.4, U3.C5, U3.K3, U3.K8, U5.2, U6.3, U6.PAD, U7.3, U7.4, U7.PAD, U8.2, U10.C, U11.1, U11.3, U12.1
NET_U1_14: R4.1, U1.14, U11.4
NET_U1_22: C9.1, C10.1, F1.1, U1.21, U1.22
NET_U1_37: R8.1, U1.37
NET_U1_76: R6.1, U1.76, U2.5
NET_U1_77: R5.1, U1.77, U2.6
NET_U1_94: R7.1, U1.94
NET_U1_98: U9.3, U9.4
NET_U2_1: R10.1, U2.1
NET_U2_2: R11.1, U2.2
NET_U2_3: R9.1, U2.3
NET_U3_C3: R15.1, U3.C3
NET_U3_C6: R12.1, U3.C6
NET_U3_C7: R14.1, U3.C7
NET_U3_C8: R16.1, U3.C8
NET_U3_D4: R13.1, U3.D4
NET_U6_1: C18.1, U6.1
NET_U6_6: R18.2, R19.1, U6.6
NET_U6_8: R17.1, U6.8
NET_U7_5: R20.1, U7.5
NET_U7_7: R21.2, R22.1, U7.7
NET_U8_1: R24.1, R25.1, U8.1
NET_U8_3: R26.2, R27.1, U8.3
NET_U8_4: R23.1, U8.4, U11.2
NET_U9_1: R2.1, U9.1, U9.2
PROC_DAC1_OUT2: U1.30, U12.2
VCC_S1_6V0: C19.1, C21.1, C24.1, C25.1, J1.1, R17.2, U6.4, U7.8
VCC_TIER1_1V8: C1.1, C2.1, C3.1, C4.1, C5.1, C6.1, C7.1, C8.1, C13.1, C17.1, C20.1, C23.1, C26.1, F1.2, R4.2, R5.2, R6.2, R9.2, R10.2, R11.2, R18.1, R23.2, R24.2, R26.1, U1.6, U1.28, U1.50, U1.75, U1.100, U2.7, U2.8, U5.4, U6.5, U8.6, U11.5
VCC_TIER1_3V0: C14.1, C15.1, C16.1, C22.1, R12.2, R13.2, R14.2, R15.2, R16.2, R20.2, R21.1, U3.H8, U3.J6, U7.1

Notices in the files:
parts and their libraries:
circuit_tree: (C) 2014 Tomasz Boleslaw CEDRO, cederom@tlen.pl, http://www.tomek.cedro.info.
